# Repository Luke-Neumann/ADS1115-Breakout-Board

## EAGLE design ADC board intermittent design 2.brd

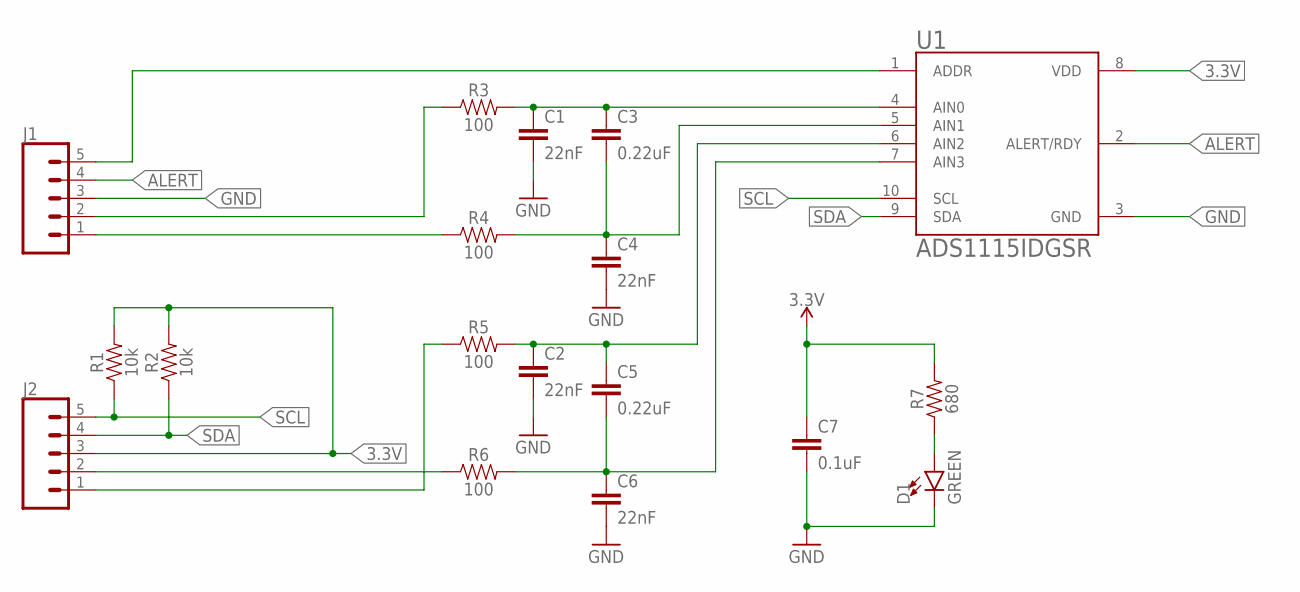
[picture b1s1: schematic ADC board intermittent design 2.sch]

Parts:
C1, C2, C4, C6: 22nF; 0603
C3, C5: 0.22uF; 0603
C7: 0.1uF; 0402
D1: GREEN; LED-0603
J1, J2: CONN_05; 1X05
R1, R2: 10k; 0603
R3, R4, R5, R6: 100; 0603
R7: 680; 0603
U1: ADS1115IDGSR; SOP50P490X110-10N

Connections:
3.3V: C7.1, J2.3, R1.2, R2.2, R7.2, U1.8 (VDD)
ALERT: J1.4, U1.2 (ALERT/RDY)
GND: C1.2, C2.2, C4.2, C6.2, C7.2, D1.C, J1.3, U1.3 (GND)
unnamed: C1.1, C3.1, R3.2, U1.4 (AIN0)
unnamed: C3.2, C4.1, R4.2, U1.5 (AIN1)
unnamed: C2.1, C5.1, R5.2, U1.6 (AIN2)
unnamed: C5.2, C6.1, R6.2, U1.7 (AIN3)
unnamed: J1.2, R3.1
unnamed: J1.1, R4.1
unnamed: J2.1, R5.1
unnamed: J2.2, R6.1
unnamed: J1.5, U1.1 (ADDR)
unnamed: D1.A, R7.1
SCL: J2.5, R1.1, U1.10 (SCL)
SDA: J2.4, R2.1, U1.9 (SDA)

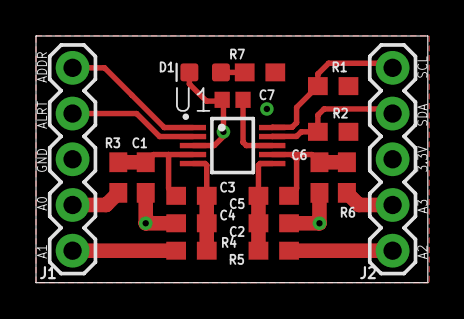
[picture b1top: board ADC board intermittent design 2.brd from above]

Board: 4 copper layers, 21.8 x 13.7 mm, 18 parts (0 on the bottom side), 15 nets.

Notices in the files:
parts and their libraries:
SparkFun-Capacitors: Licensing: Creative Commons ShareAlike 4.0 International - https://creativecommons.org/licenses/by-sa/4.0
